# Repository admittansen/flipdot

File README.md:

# flipdot
Flip dot display

Admittansen flip dot display driver
Using 2 x 3 74HC595D shift registers, Arduino nano and 24 V input.

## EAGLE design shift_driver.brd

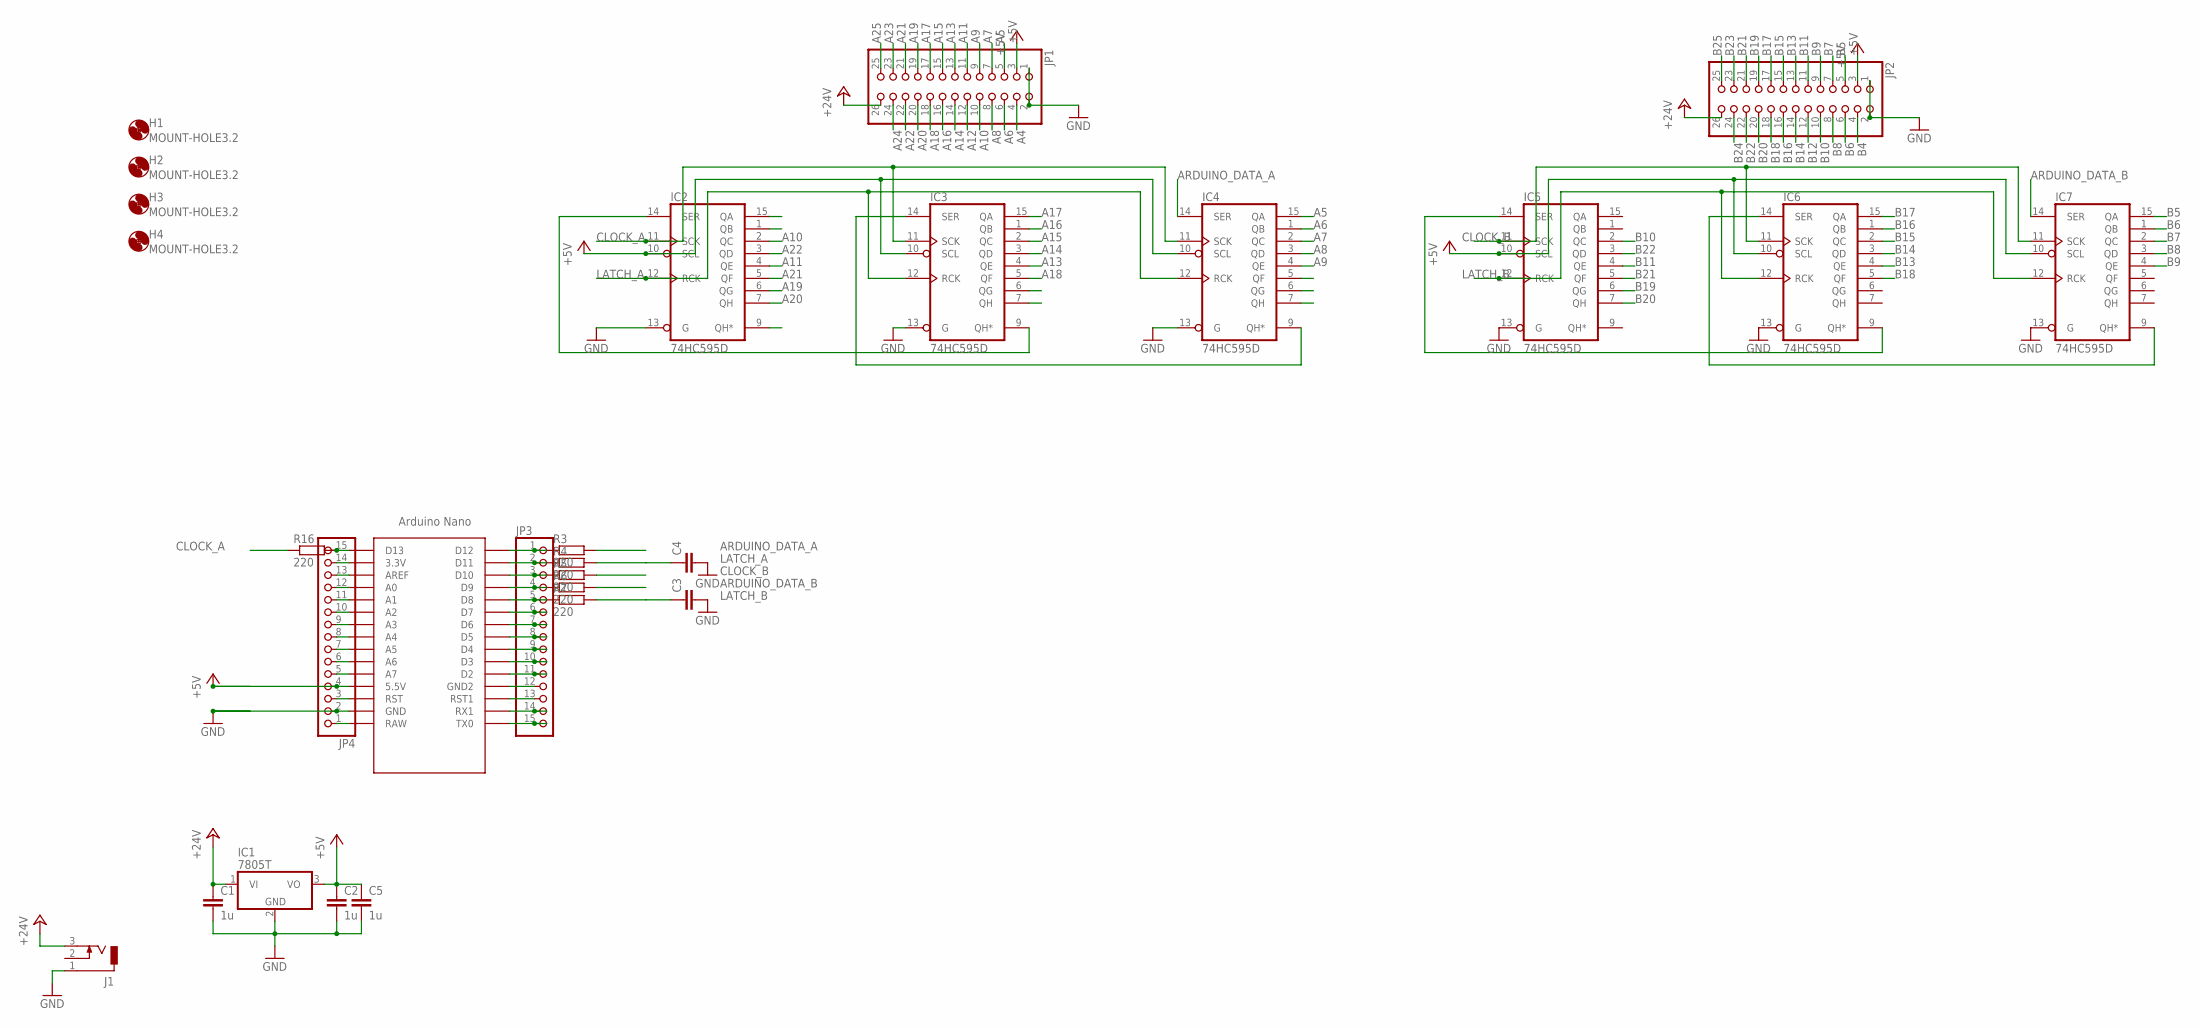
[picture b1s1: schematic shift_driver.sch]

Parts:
C1, C2, C5: 1u; C0805
C3, C4: C-EUC0805; C0805
H1, H2, H3, H4: MOUNT-HOLE3.2; 3,2
IC1: 7805T; TO220H
IC2, IC3, IC4, IC5, IC6, IC7: 74HC595D; SO16
J1: DCJ0303
JP1, JP2: PINHD-2X13; 2X13
JP3, JP4: PINHD-1X15; 1X15
R3, R4, R5, R6, R7, R16: 220; R0603
U$1: NANO

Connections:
+5V: C2.1, C5.1, IC1.3 (VO), IC2.10 (SCL), IC3.10 (SCL), IC4.10 (SCL), IC5.10 (SCL), IC6.10 (SCL), IC7.10 (SCL), JP1.3, JP2.3, JP4.4, U$1.5V (5.5V)
A4: JP1.4
A5: IC4.15 (QA), JP1.5
A6: IC4.1 (QB), JP1.6
A7: IC4.2 (QC), JP1.7
A8: IC4.3 (QD), JP1.8
A9: IC4.4 (QE), JP1.9
A10: IC2.2 (QC), JP1.10
A11: IC2.4 (QE), JP1.11
A12: JP1.12
A13: IC3.4 (QE), JP1.13
A14: IC3.3 (QD), JP1.14
A15: IC3.2 (QC), JP1.15
A16: IC3.1 (QB), JP1.16
A17: IC3.15 (QA), JP1.17
A18: IC3.5 (QF), JP1.18
A19: IC2.6 (QG), JP1.19
A20: IC2.7 (QH), JP1.20
A21: IC2.5 (QF), JP1.21
A22: IC2.3 (QD), JP1.22
A23: JP1.23
A24: JP1.24
A25: JP1.25
ARDUINO_DATA_A: IC4.14 (SER), R3.2
ARDUINO_DATA_B: IC7.14 (SER), R6.2
B4: JP2.4
B5: IC7.15 (QA), JP2.5
B6: IC7.1 (QB), JP2.6
B7: IC7.2 (QC), JP2.7
B8: IC7.3 (QD), JP2.8
B9: IC7.4 (QE), JP2.9
B10: IC5.2 (QC), JP2.10
B11: IC5.4 (QE), JP2.11
B12: JP2.12
B13: IC6.4 (QE), JP2.13
B14: IC6.3 (QD), JP2.14
B15: IC6.2 (QC), JP2.15
B16: IC6.1 (QB), JP2.16
B17: IC6.15 (QA), JP2.17
B18: IC6.5 (QF), JP2.18
B19: IC5.6 (QG), JP2.19
B20: IC5.7 (QH), JP2.20
B21: IC5.5 (QF), JP2.21
B22: IC5.3 (QD), JP2.22
B23: JP2.23
B24: JP2.24
B25: JP2.25
CLOCK_A: IC2.11 (SCK), IC3.11 (SCK), IC4.11 (SCK), R16.1
CLOCK_B: IC5.11 (SCK), IC6.11 (SCK), IC7.11 (SCK), R5.2
LATCH_A: C4.1, IC2.12 (RCK), IC3.12 (RCK), IC4.12 (RCK), R4.2
LATCH_B: C3.1, IC5.12 (RCK), IC6.12 (RCK), IC7.12 (RCK), R7.2
unnamed: IC2.14 (SER), IC3.9 (QH*)
unnamed: JP3.12, U$1.GND1 (GND2)
unnamed: JP3.13, U$1.RST1
unnamed: IC3.14 (SER), IC4.9 (QH*)
unnamed: JP4.1, U$1.RAW
unnamed: JP4.3, U$1.RST
unnamed: JP4.13, U$1.AREF
unnamed: JP4.14, U$1.3.3V
unnamed: JP3.15, U$1.TX0
unnamed: JP3.14, U$1.RX1
unnamed: JP3.11, U$1.D2
unnamed: JP3.10, U$1.D3
unnamed: JP3.9, U$1.D4
unnamed: JP3.8, U$1.D5
unnamed: JP3.7, U$1.D6
unnamed: JP3.6, U$1.D7
unnamed: JP3.5, R7.1, U$1.D8
unnamed: JP3.4, R6.1, U$1.D9
unnamed: JP3.3, R5.1, U$1.D10
unnamed: JP3.2, R4.1, U$1.D11
unnamed: JP3.1, R3.1, U$1.D12
unnamed: JP4.15, R16.2, U$1.D13
unnamed: JP4.12, U$1.A0
unnamed: JP4.11, U$1.A1
unnamed: JP4.10, U$1.A2
unnamed: JP4.9, U$1.A3
unnamed: JP4.8, U$1.A4
unnamed: JP4.7, U$1.A5
unnamed: JP4.6, U$1.A6
unnamed: JP4.5, U$1.A7
unnamed: IC5.14 (SER), IC6.9 (QH*)
unnamed: IC6.14 (SER), IC7.9 (QH*)
VCC: IC2.16 (VCC), IC3.16 (VCC), IC4.16 (VCC), IC5.16 (VCC), IC6.16 (VCC), IC7.16 (VCC)

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
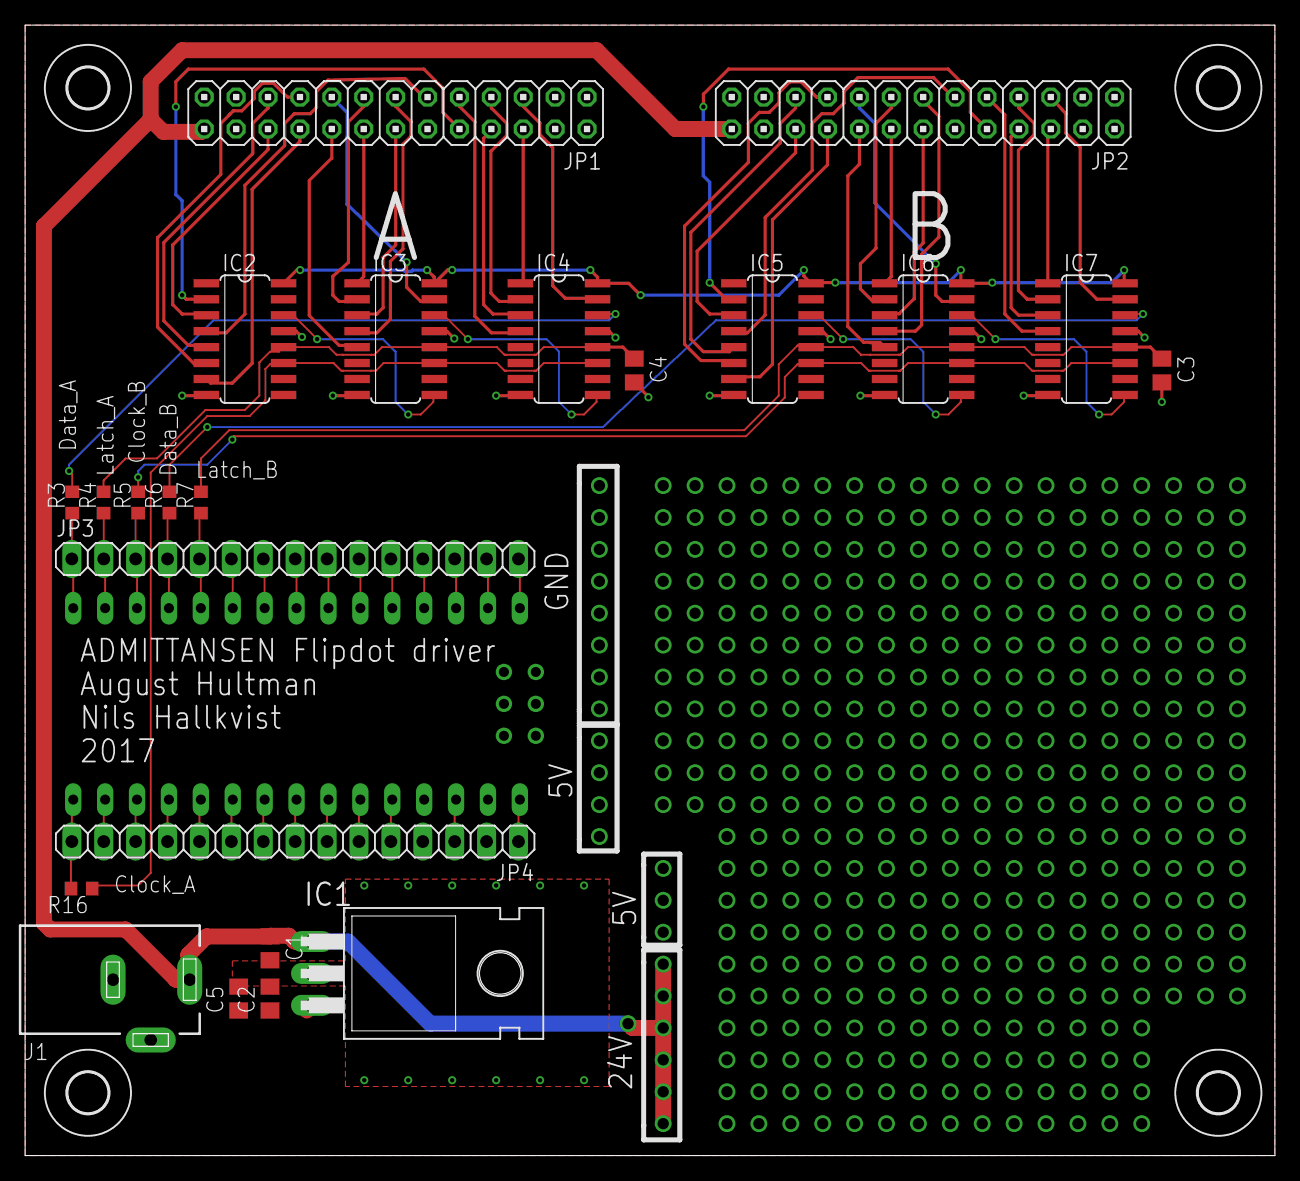
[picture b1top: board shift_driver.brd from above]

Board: 2 copper layers, 99.5 x 90.0 mm, 28 parts (0 on the bottom side), 76 nets.

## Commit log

2017-11-08 Added files from flipdot driver board project
    Under development, flipdot driver board. All wires are not routed.
2017-11-18 Routed remaining. Fixed DRC. Added proto area.
    Added design rules from seeedstudio and fixed some weird problems with
    DRC that came with it. Better clearance to everything now.
    Added a prototyping area for future expansion.
2017-12-05 Route last wires, finishing touches and small fixes.
2018-01-07 Add code and latest board file
    Code for arduino and PC
    Minor changes to board file
2018-08-19 Fix file structure of project
2019-02-17 Fix file naming to work with arduino IDE
